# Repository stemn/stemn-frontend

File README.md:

# Stemn Frontend

This repo contains all of Stemn's frontend code.

## Packages

* [stemn-frontend-website](./stemn-frontend-website) Source code for the Stemn website
* [stemn-frontend-shared](./stemn-frontend-shared) Code shared between `stemn-frontend-website` and `stemn-frontend-desktop` (consumed as source through the `stemn-shared/*` alias), plus the build conventions both apps use (`config/`)
* [stemn-frontend-desktop](./stemn-frontend-desktop) Source code for the Stemn desktop (Electron) app
* [tests/e2e](./tests/e2e) Playwright end-to-end tests of the website against a real backend

## Documentation

* [docs/ARCHITECTURE.md](./docs/ARCHITECTURE.md): how the packages, the runtime (Redux, HTTP, websocket, routing) and the conventions fit together
* [docs/DECISIONS.md](./docs/DECISIONS.md): decision records of the 2026 modernisation, including the webpack fallback policy

## Requirements

* Node.js 24 (`.nvmrc`, what CI and the Docker image use; 22.22+ works) and pnpm 12: `corepack enable` provides the
  version pinned in `package.json` (`packageManager`)

## Usage

The repo root is a [pnpm workspace](https://pnpm.io/workspaces) (`pnpm-workspace.yaml`) containing
`stemn-frontend-shared`, `stemn-frontend-website`, `stemn-frontend-desktop` and `tests/e2e`. There is a single
`pnpm-lock.yaml` at the root. Versions used by more than one package live in the `catalog:` of `pnpm-workspace.yaml`.
`node_modules` is pnpm's isolated layout: a package can only import what its own `package.json` declares.

```sh
pnpm install          # install everything (run at the repo root)
pnpm run dev          # website: Vite dev server with React Fast Refresh on http://localhost:8081
pnpm run build        # website: Vite production build -> stemn-frontend-website/build
pnpm run serve        # serve the production build on http://localhost:8081 (PORT=... to change)
pnpm run dev:webpack  # website: the webpack 5 fallback dev server (same port)
pnpm run build:webpack # website: the webpack 5 fallback production build (same output dir)
pnpm run typecheck    # tsc --noEmit: website, desktop, e2e (type errors never block the builds)
pnpm run lint         # ESLint (--max-warnings 0) + Prettier check; pnpm run lint:fix / pnpm run format fix them
pnpm test             # unit tests (Vitest)
pnpm run test:e2e     # website end-to-end tests (Playwright) against the local backend, see tests/e2e/README.md
```

The website talks to the Stemn backend. By default (`STEMN_ENV=local`) it expects the API on
http://localhost:3000 and the websocket (Primus) server on http://localhost:8000.
See [stemn-frontend-website/README.md](./stemn-frontend-website/README.md) for the other environments.

A husky pre-commit hook runs ESLint and Prettier on the staged files (lint-staged). `HUSKY=0` skips it.

## Continuous integration

GitHub Actions (`.github/workflows`):

* `ci.yml` on every pull request and on pushes to `staging` / `production`: lint, typecheck, unit tests, builds (website with
  Vite, website with the webpack fallback, desktop), the website Docker image, and `e2e`.
* `e2e.yml` (reusable, `workflow_call`): starts the backend (`.github/actions/stemn-backend`: checks out the private
  `stemn-backend` with a read-only deploy key, `local/start.sh` + `local/seed.sh`), then runs the website Playwright suite and the
  desktop suite under `xvfb-run`. Traces, screenshots and backend logs are uploaded when it fails.
* `codeql.yml` (JavaScript/TypeScript code scanning) and `dependency-review.yml` (blocks pull requests that add dependencies with
  high-severity advisories). Renovate (`renovate.json`) opens grouped dependency updates against `staging`.

## Running the full stack locally

The backend lives in the sibling `stemn-backend` repository (branch `modernize/2026`). Everything below is
documented in detail in `stemn-backend/local/README.md`.

```sh
# 1. backend: MongoDB + Redis in Docker, API on :3000, websocket server on :8000
cd ../stemn-backend && local/start.sh        # local/stop.sh stops it; local/smoke-test.sh re-checks the API

# 2. demo data (idempotent): 8 users, 14 projects, files, threads, comments, follows
local/seed.sh                                 # all demo accounts use the password "password123"
                                              # e.g. ada.lovelace@stemn.local, priya.raman@stemn.local

# 3. website
cd ../stemn-frontend && pnpm install && pnpm run dev   # http://localhost:8081
```

Port 8080 is deliberately avoided because the development container's noVNC server listens there.

## Desktop

The Electron app lives in [stemn-frontend-desktop](./stemn-frontend-desktop) (Electron 45,
electron-vite 6 / Vite 8, React 19, the same shared code as the website). From the repo root:

```sh
pnpm run desktop:dev        # main + preload in watch mode, renderer dev server with Fast Refresh, launches Electron
pnpm run desktop:build      # production build -> stemn-frontend-desktop/dist (STEMN_ENV=production unless set)
pnpm run desktop:start      # run the built app
pnpm run desktop:package    # Linux AppImage + unpacked dir -> stemn-frontend-desktop/release
pnpm run desktop:test:e2e   # Playwright + Electron end-to-end test against the local backend (needs a display)
pnpm run desktop:typecheck
```

`desktop:dev` talks to the local backend (`STEMN_ENV=local`: API :3000, websocket :8000). On Linux the
Electron sandbox helper must be setuid root, and `ELECTRON_RUN_AS_NODE` must not leak into the app (the
scripts strip it). See [stemn-frontend-desktop/README.md](./stemn-frontend-desktop/README.md) for the
architecture, the security model (context isolation + sandbox + preload bridge, no `remote`),
environment variables and packaging for Windows/macOS.

## Open Source Contributions

If you want to contribute a feature, please contact us 😊

## Related Repos

* [stemn-desktop](https://github.com/stemn/Stemn-Desktop) the production releases of the stemn-desktop app (produced from this src)

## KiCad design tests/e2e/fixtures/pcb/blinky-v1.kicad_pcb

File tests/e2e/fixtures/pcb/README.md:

# PCB fixtures

Byte-identical copies of stemn-backend's shared PCB samples (`services/api/src/core/__tests__/samples/pcb`, generated by that
directory's `generate-samples.py`). The backend's PCB converter tests, the API's render and diff tests and these website e2e tests
use the same files. Copy them again when the backend samples are regenerated; do not edit them.

- `blinky-v1.kicad_pcb` → `blinky-v2.kicad_pcb`: two revisions of a small KiCad board with one change of each class (test point
  TP1 added, C2 removed, R2 swapped from 0603 to 0805: modified, R1 turned 90 degrees: moved, the rest unchanged), for
  `specs/pcb.spec.ts`
- `blinky-v1.kicad_sch`: the board's schematic, for the preview test
- `samples.json`: what each sample converts to, and the entity ids of each class between the revisions

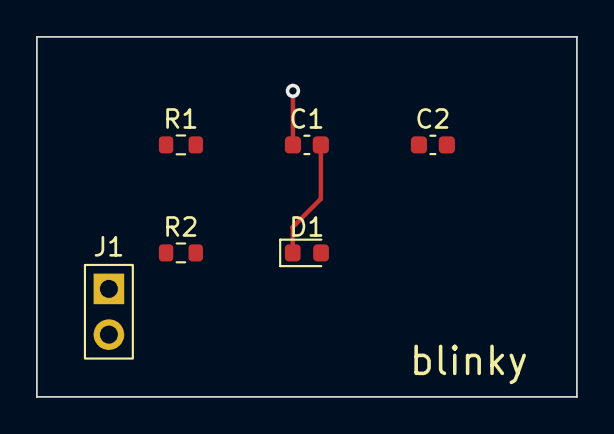
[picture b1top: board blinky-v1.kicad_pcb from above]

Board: 2 copper layers, 30.0 x 20.0 mm, 6 parts (0 on the bottom side), 5 nets.

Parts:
C1: 100n; C_0603_1608Metric
C2: 10u; C_0603_1608Metric
D1: red; LED_0603_1608Metric
J1: Conn_01x02; PinHeader_1x02_P2.54mm_Vertical
R1: 10k; R_0603_1608Metric
R2: 1k; R_0603_1608Metric

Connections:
GND: C1.1, C2.2, J1.2
LED: C1.2, D1.1
N1: R1.2, R2.1
N2: D1.2, R2.2
VCC: C2.1, J1.1, R1.1

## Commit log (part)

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2018-06-06 Add travis
2018-06-06 Update travis
2018-06-06 Update CI script
2018-06-06 Add empty folder
2018-06-06 Add empty deploy script
2018-06-06 goob
2018-06-06 remove assets folder
2018-06-06 moved more stuff
2018-06-06 broken
2018-06-06 Misc
2018-06-08 Add clone button
2018-06-08 Added clone
2018-06-08 Add deploy script
2018-06-08 update deploy docs
2018-06-08 fix ci script
2018-06-08 update deploy script
2018-06-08 Add env note
2018-06-08 Add github token
2018-06-08 Add token
2018-06-08 Add build number
2018-06-08 Add build to cache
2018-06-08 Add adoc and csv to supported code file types
2018-06-09 update css import
2018-06-09 Update uglify
2018-06-09 Add no errors plugin
2018-06-09 Add link script
2018-06-10 Add link
2018-06-11 Add clone link
2018-06-22 Change to autodesk hosted viewer
2018-07-01 Added cancel pipeline function
2018-07-01 Add fav and theme config
2018-07-02 Seems to work
2018-07-02 exports fixed
2018-07-02 Fixed auth
2018-07-02 Fix loading view
2018-07-02 Add default
2018-07-02 Use stemn/whats-that-gerber
2018-07-03 Moved to PropTypes
2018-07-03 update react-router
2018-07-03 Remove createClass
2018-07-03 Homepage loading with new react
2018-07-03 Fixed contextmenu
2018-07-03 Ununsed imports removed
2018-07-03 Remove unused vars
2018-07-04 Fixed === and !==
2018-07-04 Rename classNames as cn
2018-07-04 Fix is mention
2018-07-04 Add circleci yaml
2018-07-04 Add sudo
2018-07-04 Add link:shared
2018-07-04 remove old scripts
2018-07-04 Adding tests
2018-07-04 Remove lint
2018-07-04 Add bitwise operator
2018-07-04 Fix upload
2018-07-04 tests working
2018-07-04 Add cypress
2018-07-04 Cache happypack
2018-07-04 Fix cypress run
2018-07-04 Add cypress install
2018-07-04 Add build staging option
2018-07-04 update node version
2018-07-04 change to npm-deps
2018-07-04 remove spread
2018-07-04 move
2018-07-05 borke
2018-07-05 hmm...
2018-07-05 fix for else
2018-07-05 Add back test e2e
2018-07-05 Add stemn_env
2018-07-05 Add sudo run script
2018-07-05 gooba
2018-07-05 Save npm and cache to workspace
2018-07-05 install cypress
2018-07-05 change
2018-07-05 website
2018-07-05 update command
2018-07-05 [ci skip]
2018-07-05 Fix indenting
2018-07-05 update docs [ci skip]
2018-07-05 Add toc
2018-07-05 updated tag in deploy script
2018-07-07 Add storm diagrams
2018-07-07 ts changes
2018-07-08 move module
2018-07-08 pushing for david
2018-07-08 json schema
2018-07-09 Add custom node
2018-07-09 Add pipeline types
2018-07-09 Add css
2018-07-09 removed story book
2018-07-09 trailing comma
2018-07-10 base template layout figured
2018-07-10 attach launch configuration for vs code
2018-07-10 working
2018-07-11 Working!
2018-07-11 add tests
2018-07-11 test passing
2018-07-11 Working Model with email, text, password widgets implemented
2018-07-11 fix ts error
2018-07-11 Added date picker and fixed onChange events
2018-07-11 fixed padding around block titles
2018-07-11 TextArea, Upload and Date Widgets for JsonSchema
2018-07-11 Update scherma
2018-07-11 some theming
2018-07-11 morning cleanup
2018-07-11 cleaned up the example schema
2018-07-11 cleaned up jsonschema form
2018-07-11 yaml loading
2018-07-11 Add node tables
2018-07-11 Add sidebar widgets
2018-07-12 onChange event working on text input
2018-07-12 Unfinished Date code
2018-07-12 disabled broken widgets for now
2018-07-12 fixed up the example schema for textarea
2018-07-12 fixed textarea formatting
2018-07-12 Select Widget
2018-07-12 Fixed submit being called on any button press
2018-07-12 removed duplicate description
2018-07-12 dropdown of type button
2018-07-12 fixed onChange handler in Textarea
2018-07-12 Fixed required fields
2018-07-12 msic
2018-07-13 update deps
2018-07-13 fix lint issues
2018-07-13 fixed the format fields in the uischema so they no longer break the form validation
2018-07-13 Moved the format transformation function out into their own utils file
2018-07-13 code cleanup for linter
2018-07-13 Added custom error messages
2018-07-13 Some of the requested changes and removed unused files
2018-07-13 Removed date
2018-07-15 Added error animations
2018-07-15 Checkbox styling and on errors the text boxes now appear red
2018-07-15 Cleaned up the layout and aggregated some of the visual elements
2018-07-15 Ok ...
2018-07-19 add schema
2018-08-01 Add cypress record
2018-08-02 add any type hack
2018-08-02 Added tslint
2018-08-02 Add back lint
2018-08-02 Make pure
2018-08-02 Add cast
2018-08-02 Add namespace to kubectl image set
2018-08-02 Don't minify
2018-08-02 Change install
2018-08-10 potential-fix for linux build
2018-08-10 removed cypress as a dependency
2018-08-10 updated cache dependency keys
2018-08-10 fixing desktop and adding analytics
2018-08-12 Desktop is working
2018-08-12 update packages
2018-08-12 fix lock files
2018-08-12 updated build script
2018-08-12 Add webpack cli
2018-08-12 sudo install
2018-08-12 remove sudo
2018-08-12 Minify prod
2018-08-12 release
2018-08-12 remove old build script
2018-08-12 rename install
2018-08-12 Add deploy prompt
2018-08-12 Fix name
2018-08-12 fix deploy desktop
2018-08-12 Update build scripts
2018-08-16 remove export
2018-08-16 deploy after tests
2018-08-16 Add analytics page tracks
2018-08-16 Change auth config for staging
2018-08-16 Auth config
2018-08-23 fix build
2018-08-23 Desktop settings fixed
2018-08-23 Fix preview markdown
2018-08-23 Fix desktop preview page loading
2018-08-26 Change includes
2018-08-26 Update lock
2018-08-26 Update ci config
2018-08-26 Remove yarn error
2018-08-27 Misc desktop improvments
2018-08-27 Fix circleci approval
2018-08-27 Update desktop deploy script
2018-08-29 Convert project row and explore page to typescript
2018-08-30 Add featured tiles
2018-08-30 Explore page working with contentful
2018-08-30 Updates project row view
2018-08-30 Add info icons to project rows
2018-08-30 Lint fix
2018-08-30 Disablke no use before declare
2018-09-06 Add jsx tslint rules
2018-09-06 Convert file to ts
2018-09-06 Fix file page
2018-09-07 Add upload modal
2018-09-07 Add redux form
2018-09-07 Add file upload
2018-09-08 File upload
2018-09-08 new script
2018-09-08 merge
2018-09-08 script run
2018-09-08 reverse dep fuckup
2018-09-09 Fix upload endpoint
2018-09-12 Add fileList types
2018-09-13 Fix promise middleware export
2018-09-13 Remove default
2018-09-13 Cypress tests in ts
2018-09-13 Convert cypress to ts
2018-09-15 Add Edit Button
2018-09-15 Add ts to files and file compare menu
2018-09-16 Add mode type
2018-09-16 Change actions to ts
2018-09-16 Update actions
2018-09-16 Convert PreviewFile to ts
2018-09-16 Conver compare to ts
2018-09-16 Fix fetchTimeline changes
2018-09-16 Lint fixes
2018-09-16 Fix codemirror import
2018-09-16 Remove scroll bars on file page
2018-09-16 Upade SimpleIconButton to ts
2018-09-18 lockfile
2018-09-18 missing deps
2018-09-18 more deps
2018-09-18 Add button types
2018-09-18 Revert "more deps"
    This reverts commit 37127d2f5aed609a8ac06ec6f75c10972995064f.
2018-09-18 Revert "missing deps"
    This reverts commit 1636a4e35c7c8dc60c535534e030c94e144c5e62.
2018-10-04 bump node-sass to 4.9.3
2018-10-04 Revert "bump node-sass to 4.9.3"
    This reverts commit ae12c3787666ad0b46f2d221d1f88949acd02feb.
2018-10-04 new scripts
2018-10-05 Desktop working
2018-10-05 Revert "new scripts"
    This reverts commit 51ecdc19e9b4a850e721aac4ec71d8cd0a7aedf7.
2018-10-06 make scripts generic
2018-10-06 swap id order
2018-10-07 use npm ci
2018-10-07 fix dep order
2018-10-07 ci shared
2018-10-07 use node 10.11
2018-10-07 fix bad package-lock.json
2018-10-07 top level redux
2018-10-07 building
2018-10-12 Fix editor and textarea focus
2018-10-28 Default file list path to remote root
2018-11-07 fix tokens and url
2018-11-08 use fileId
2018-11-08 http method
2018-11-08 dfaults
2018-11-09 various fixes
2018-11-09 file id
2018-11-18 fix timeline call
2018-11-19 primary email fix
2018-12-02 custom env
2018-12-29 scripts
2019-01-06 upgrade-sass
2019-01-31 no-and
2019-02-12 no-integrity
2019-02-13 add-concurrency
2019-03-24 crash
